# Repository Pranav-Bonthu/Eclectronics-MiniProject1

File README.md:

# Eclectronics Mini-Project 1
Final right up can be found here: ['docs/Electronics-Mini-Project-1.pdf'](docs/Electronics-Mini-Project-1.pdf)

---

## Simulation

200-run Monte Carlo over 1 % resistor and 5 % capacitor tolerances:

---

## Schematic

PDF: [`docs/kicad-schematic.pdf`](docs/kicad-schematic.pdf)

---

## The board

| Top | Bottom |
|---|---|
|  |  |

| Front (F.Cu ) | Back (B.Cu) |
|---|---|
|  |  |

---

## Repository layout

```
kicad/        KiCad 10 project: schematic, board, and the
              symbol/footprint libraries it depends on
ltspice/      Simulation and results
fabrication/  Gerbers 
docs/         Project write-up and schematic PDF
images/       Images for the README    
```

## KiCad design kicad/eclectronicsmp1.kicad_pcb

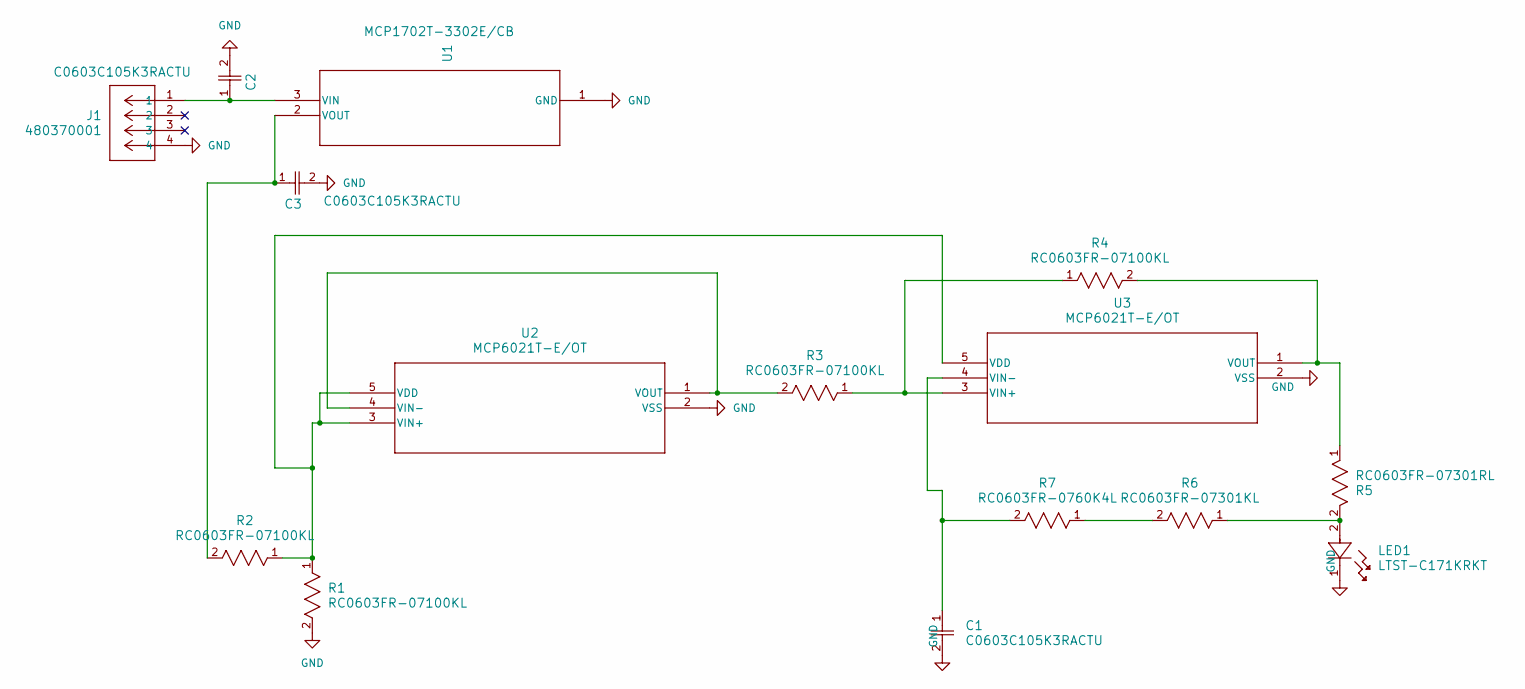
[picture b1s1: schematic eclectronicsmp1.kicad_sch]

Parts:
C1, C2, C3: C0603C105K3RACTU; CAPC17595_95N_KEM
J1: 480370001; CONN_480370001_MOL
LED1: LTST-C171KRKT; LED_LTST-C171_LTO
R1, R2, R3, R4: RC0603FR-07100KL; RC0603N_YAG
R5: RC0603FR-07301RL; RC0603N_YAG
R6: RC0603FR-07301KL; RC0603N_YAG
R7: RC0603FR-0760K4L; RC0603N_YAG
U1: MCP1702T-3302E/CB; SOT-23A_MC_MCH
U2, U3: MCP6021T-E/OT; SOT-23-5_MC_MCH

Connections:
GND: C1.2, C2.2, C3.2, J1.4, LED1.1, R1.2, U1.1 (GND), U2.2 (VSS), U3.2 (VSS)
unnamed: LED1.2, R5.2, R6.1
unnamed: R6.2, R7.1
unnamed: C2.1, J1.1, U1.3 (VIN)
unnamed: C3.1, R2.2, U1.2 (VOUT)
unnamed: R1.1, R2.1, U2.3 (VIN+), U2.5 (VDD), U3.5 (VDD)
unnamed: R3.2, U2.1 (VOUT), U2.4 (VIN-)
unnamed: R3.1, R4.1, U3.3 (VIN+)
unnamed: C1.1, R7.2, U3.4 (VIN-)
unnamed: R4.2, R5.1, U3.1 (VOUT)

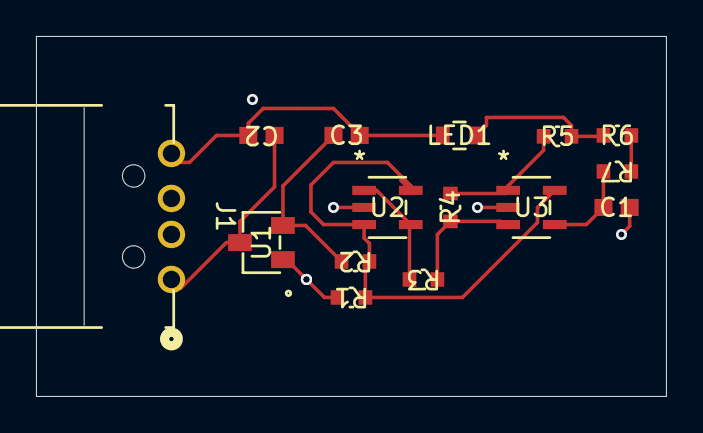
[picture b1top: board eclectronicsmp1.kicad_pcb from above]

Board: 2 copper layers, 35.0 x 20.0 mm, 15 parts (0 on the bottom side), 10 nets.
